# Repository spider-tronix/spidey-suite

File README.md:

# spidey-suite

spidey suite is the smart choice for Over The Air(OTA) Programming solution for your AVR microcontrollers. It has products ranging from bootloader to code uploader/downloader for your device, all in the same module.

## Products 

spidey suite has 3 products to offer and they are- 
- ```spideyboot``` - A small light weight bootloader with just the OTA Programmming functionality. More info [here](https://github.com/spider-tronix/spidey-suite/tree/master/spideyboot)
- ```spideydude``` - Code uploader for spideyboot. More info [here](https://github.com/spider-tronix/spidey-suite/tree/master/spideydude)
- ```spideyAVRdude``` - OTA code uploader for the boards having Arduino's Optiboot bootloader. More info [here](https://github.com/spider-tronix/spidey-suite/tree/master/spideyAVRdude)

## Contents of this repository

> To be updated

## Bug Reports and Improvements

-  To report a ***bug*** in the software or to request *an enhancement*, create an [*issue*](https://github.com/spider-tronix/spidey-suite/issues) clearly stating the problem. Our team will look into the problem and will fix it as soon as possible.

- To suggest *changes/improvements*, create a [*pull-request*](https://github.com/spider-tronix/spidey-suite/pulls) with the modified files. Upon successfully validating the changes by us, the suggested changes will be added to the repository.

## Website

Click [**here**](https://spider-tronix.github.io/spidey-suite/) to navigate to the website. 

The website is developed and maintained by our team only. It uses a number of web development tech and those are:

* [ReactJS](https://reactjs.org/) - React is an open-source, front end, JavaScript library for building user interfaces or UI components.
* [Bootstrap](https://getbootstrap.com/) - Bootstrap is a free and open-source CSS framework directed at responsive, mobile-first front-end web development.
* [jQuery](https://jquery.com/) - jQuery is an open-source, free JavaScript library designed to simplify HTML DOM tree traversal and manipulation, as well as event handling, CSS animation, and Ajax

For more info on the website, click [here](https://github.com/spider-tronix/spidey-suite/tree/master/Build/Code/Web/spidey-suite).

## Credits

spidey suite is an open source project started by [**Spider Tronix**](https://spider-tronix.github.io/) profile under [**Spider R&D Club**](https://spider.nitt.edu/) of **NIT Trichy**.

The spidey suite team is composed of [Aditya Kumar Singh](https://github.com/adityasingh3007), [Miriam](https://github.com/Githubmsk), [Arunesh Saddish](https://github.com/arunesh006), [N Srikrishna](https://github.com/2001srikrishna)

# PROJECT UNDER DEVELOPMENT PHASE

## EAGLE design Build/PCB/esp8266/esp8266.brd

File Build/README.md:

# Build
This folder contains the build(source) files for the various products under spidey suite.  

# spidey suite
A module to add OTA Programming functionality to AVR Microcontrollers

## Abstract
OTA (Over the Air) Programming is a process which allows devices to upgrade their firmware or software wirelessly without any physical access. It uses wireless technology like Wi-Fi, Bluetooth, GPRS or 4G/3G rather than wired serial communication. OTA is used to reprogram the devices like microcontrollers, cell phones, computers, set-top box etc in order to add some feature, resolve some bugs, etc. The project aims to make a module which can be attached to any AVR microcontroller in order to add OTA Programming feature to it. The module will be just like any other peripheral sensor modules with few pins left open for the user to connect it to their circuit. The module will be cost effective and as minimum space consuming as possible. Also, a web portal will be developed where in the corresponding codes for the target μC for example – Arduino UNO/Mega/Nano can be downloaded and configured as per the user’s requirement. And a dedicated HTTP interface wherein the codes can be sent over the air.

# Status
#### Phase 1:
- Understanding complete memory architecture of a μC
- Understanding bootloader, how OTA works.
- How a program is transferred in the μC. 
- How to write a light weight custom bootloader which can be added on top of an existing bootloader so that the μC can still be programmed from Arduino IDE (if using Arduino boards). 
- If that’s not feasible (considering memory consumption by two bootloaders), how to write a standalone bootloader. 

#### Phase 2:
- Implementing the understanding done in the previous phase in the UNO and Mega boards. 
- Developing the portal
- Generalising the code in order to target more than 1 μC with the same code if possible (due to same architecture) 

# Team:
  - Aditya Kumar Singh [https://github.com/adityasingh3007] 
  - Miriam [https://github.com/Githubmsk]
  - Arunesh Saddish [https://github.com/arunesh006]
  - N Srikrishna [https://github.com/2001srikrishna]

## NOTE: Project under development phase.

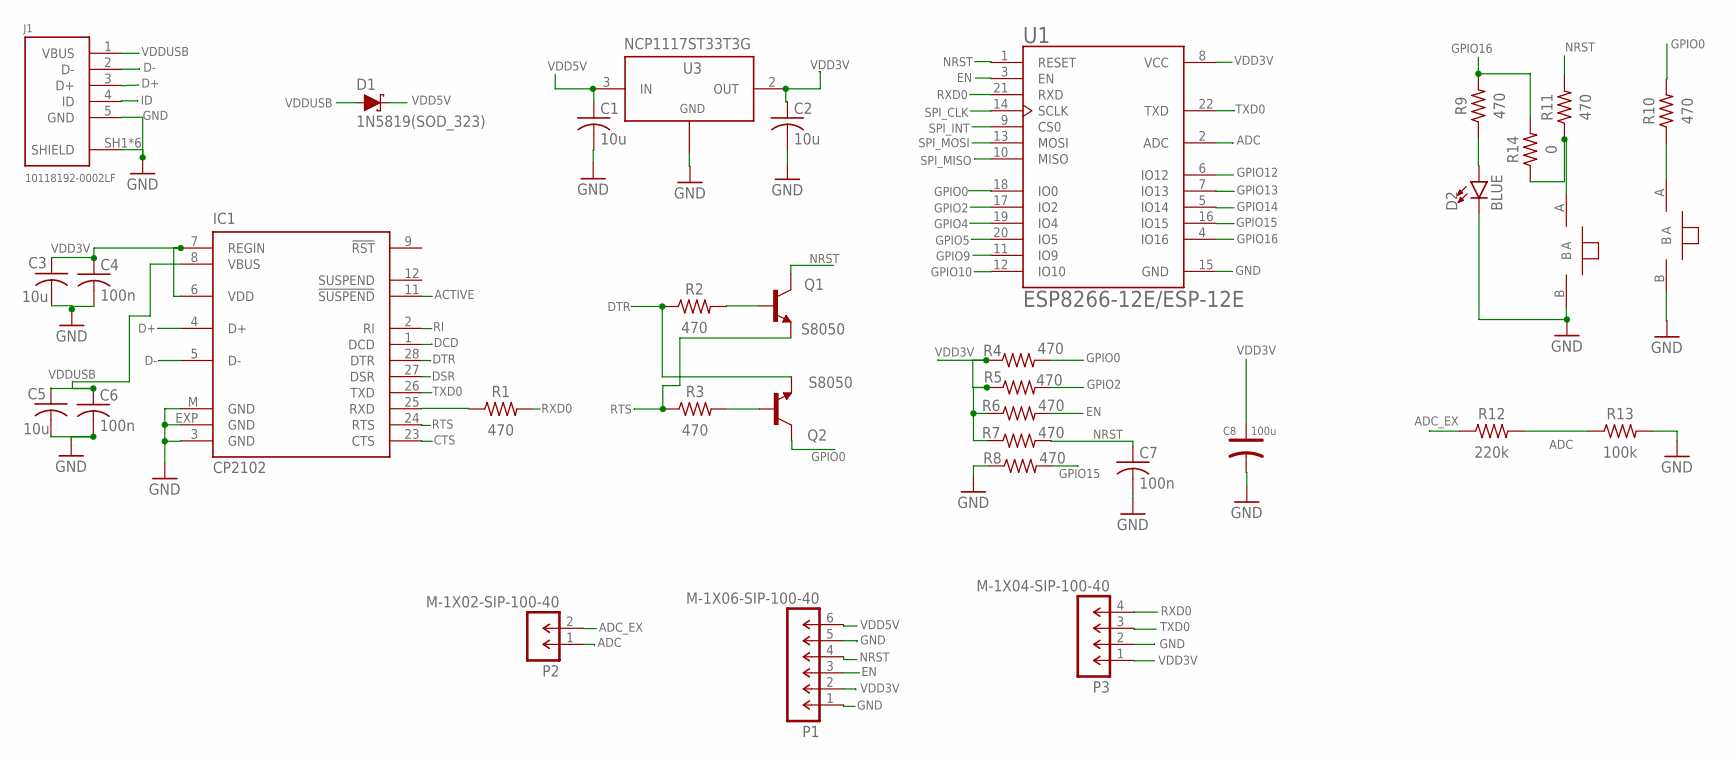
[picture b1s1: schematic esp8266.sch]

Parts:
C1: 10u; CAPC2012X110
C2, C3, C5: 10u; CAPC1005X60
C4, C6, C7: 100n; CAPC1005X60
C8: 100u; AVX-B
D1: 1N5819(SOD_323); SOD-323
D2: BLUE; LED-0603
IC1: CP2102; MLP28
J1: 10118192-0002LF
P1: M-1X06-SIP-100-40; SIP-100-06-40
P2: M-1X02-SIP-100-40; SIP-100-02-40
P3: M-1X04-SIP-100-40; SIP-100-04-40
Q1, Q2: S8050; SOT23
R1, R2, R3, R4, R5, R6, R7, R8, R9, R10, R11: 470; RESC1005X40
R12: 220k; RESC1005X40
R13: 100k; RESC1005X40
R14: 0; RESC1005X40
U1: ESP8266-12E/ESP-12E; XCVR_ESP8266-12E/ESP-12E
U3: NCP1117ST33T3G; SOT-223
U$2, U$3: PT_820

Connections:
ACTIVE: IC1.11 (!SUSPEND)
ADC: P2.1, R12.2, R13.1, U1.2 (ADC)
ADC_EX: P2.2, R12.1
CTS: IC1.23 (CTS)
D+: IC1.4 (D+), J1.3 (D+)
D-: IC1.5 (D-), J1.2 (D-)
DCD: IC1.1 (DCD)
DSR: IC1.27 (DSR)
DTR: IC1.28 (DTR), Q2.2 (E), R2.1
EN: P1.3, R6.2, U1.3 (EN)
GND: C1.2, C2.2, C3.2, C4.2, C5.2, C6.2, C7.2, C8.-, D2.C, IC1.3 (GND), IC1.EXP (GND), IC1.M (GND), J1.5 (GND), J1.SH1 (SHIELD), J1.SH2 (SHIELD), J1.SH3 (SHIELD), J1.SH4 (SHIELD), J1.SH5 (SHIELD), J1.SH6 (SHIELD), P1.1, P1.5, P3.2, R8.1, R13.2, U1.15 (GND), U3.1 (ADJ/GND), U$2.B, U$3.B
GPIO0: Q2.3 (C), R4.2, R10.2, U1.18 (IO0)
GPIO2: R5.2, U1.17 (IO2)
GPIO4: U1.19 (IO4)
GPIO5: U1.20 (IO5)
GPIO9: U1.11 (IO9)
GPIO10: U1.12 (IO10)
GPIO12: U1.6 (IO12)
GPIO13: U1.7 (IO13)
GPIO14: U1.5 (IO14)
GPIO15: R8.2, U1.16 (IO15)
GPIO16: R9.2, R14.2, U1.4 (IO16)
ID: J1.4 (ID)
unnamed: D2.A, R9.1
unnamed: Q1.1 (B), R2.2
unnamed: R11.1, R14.1, U$2.A
unnamed: Q2.1 (B), R3.2
unnamed: R10.1, U$3.A
NRST: C7.1, P1.4, Q1.3 (C), R7.2, R11.2, U1.1 (RESET)
RI: IC1.2 (RI)
RTS: IC1.24 (RTS), Q1.2 (E), R3.1
RX: IC1.25 (RXD), R1.1
RXD0: P3.4, R1.2, U1.21 (RXD)
SPI_CLK: U1.14 (SCLK)
SPI_INT: U1.9 (CS0)
SPI_MISO: U1.10 (MISO)
SPI_MOSI: U1.13 (MOSI)
TXD0: IC1.26 (TXD), P3.3, U1.22 (TXD)
VDD3V: C2.1, C3.1, C4.1, C8.+, IC1.6 (VDD), IC1.7 (REGIN), P1.2, P3.1, R4.1, R5.1, R6.1, R7.1, U1.8 (VCC), U3.2 (OUT), U3.4
VDD5V: C1.1, D1.C, P1.6, U3.3 (IN)
VDDUSB: C5.1, C6.1, D1.A, IC1.8 (VBUS), J1.1 (VBUS)

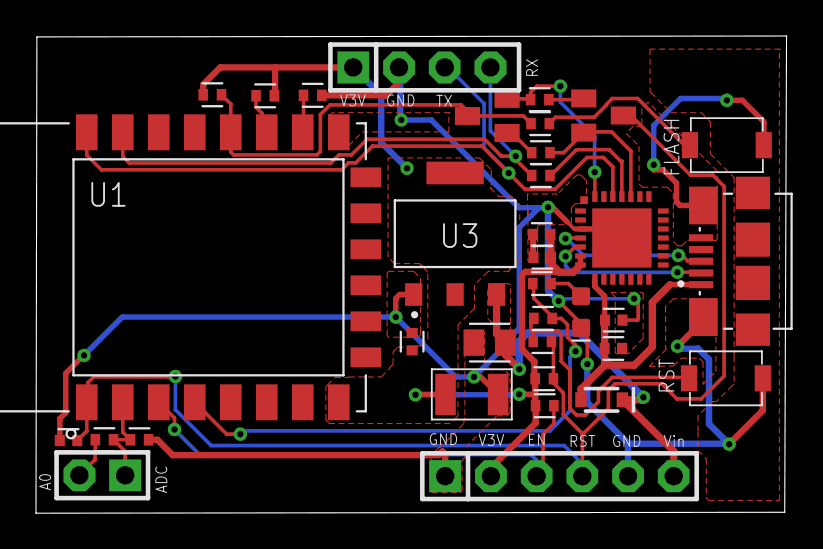
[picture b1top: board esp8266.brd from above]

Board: 2 copper layers, 41.7 x 26.5 mm, 35 parts (0 on the bottom side), 24 nets.

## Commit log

2020-09-22 Resources, gitignore added. Readme updated
2020-09-22 Github profile link added
2020-09-25 Code to read signature and fuse bytes added
2020-09-27 Few other resources added
2020-09-27 Basic fixed prog. bootloader code added
2020-09-29 AVRDUDE executable added
2020-09-29 BLDR base testing code added
2020-09-29 Cheatsheet for avrdude added
2020-09-29 avrdude cheatsheet errro fixed. Basic_BLDR code logic modified:
2020-10-02 Checking MCUSR reg logic added
2020-10-04 Server files for transferring HEX file added
2020-10-05 EXTRF logic rectified
2020-10-08 usart func added
2020-10-08 Optiboot logic txt file, esp32 softAP mode code added
2020-10-09 ESP32 server client code for uploading hex file added
2020-10-09 UART Reciever Code Rectified
2020-10-10 UART and Watchdog utility codes added
2020-10-11 ESP32 SPIFFS file uploading via station mode code added
2020-10-12 Code having AP+STA feature added. STA standalone code credentials fixed.
2020-10-16 Routing corner cases logic added
2020-10-16 avrdude replica for esp32 base code added
2020-10-18 avrdude client code converted to lib files. Snip of output added
2020-10-19 SpideyBoot code for ESP32 added
2020-10-19 SpideyBoot for esp32 renamed to Spideydude
2020-10-19 Spideydude HTTP Server added
2020-10-19 Spideyboot bootloader code added
2020-10-19 SpideyBoot Code Added
2020-10-20 Spideyserver lib file for Spideydude added. Helper .py and .htm files added
2020-10-20 spideydude verbose sent as reponse to server part added
2020-10-21 Optiboot logic updated
2020-10-22 response sending data back to server part added
2020-10-24 Code to get Signature Bytes and Read a page from flash added in SpideyBoot
2020-10-25 Phase 2 initiated. Readme updated
2020-10-25 gitignore added
2020-10-25 Spideyboot program to read flash updated
2020-10-25 Web portal base added
2020-10-26 spideydude protocol lib changes added
2020-10-26 Contribute and Footer section added
2020-10-26 spideydude read signature bytes logic added
2020-10-27 Read Flash Error and Spidey Protocol Updated
2020-10-27 SpideyProtocol Updated
2020-10-27 WATCHDOG timer code documented.
2020-10-27 Product section added. Footer bug fixed. Minor UI change
2020-10-29 Hex parser v.0
2020-10-29 maximum bootsize and optiboot usage data added to signature .ino
2020-10-29 minor changes
2020-10-31 Organizing directories
2020-10-31 Readmes updated
2020-10-31 Typo fixed
2020-10-31 WDG and UART Lib Merged
2020-10-31 Code to Check Flash Corrected
2020-11-01 Web portal Feature and Product section added. Name changing done
2020-11-01 LICENSE added
2020-11-02 HexParser testing code
2020-11-04 Protocol.md and Code documentation added
2020-11-05 Documentation enhanced. Minor bug fixed
2020-11-05 Updated HexParser
2020-11-05 Spideyboot production code added. Protocol.md modified
2020-11-07 HEX Parser data handling bug fixed. Hex parser added to spideydude. Addressing bug fix in spideydude.
2020-11-13 the helper library with the signchk and bytetohex func
2020-12-10 Signature verification added in Spideydude
2020-12-10 Spideydude v0.9.2 production code added
2020-12-10 hexParser and Signature module added to esp32_avrdude
2020-12-11 Updated PROTOCOL.md
    Fixed typos and confusing statements.
2020-12-11 Updated main README and Build/Readme
2020-12-11 Dupicates removed. SpideyAVRdude production coded added
2020-12-12 Spideyboot: Optimized the pagelength data storing -v0.7.0 update
2020-12-13 Flash Size check, auto pageSize detection added
2020-12-17 Prod. dropped. PCB for the mdoule added
2020-12-23 Images added. Readme updated
2020-12-23 Update readme with images link
2020-12-29 Readmes updated. Images and sample hex codes added
2020-12-29 spideybootd readme updated. Sample hex file added
2021-01-19 Minor broken links fixed
2021-01-19 Minor broken links fixed.
2021-01-21 Webpage header added. Other minor improvements

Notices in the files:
parts and their libraries:
SparkFun-DiscreteSemi: Licensing: Creative Commons ShareAlike 4.0 International - https://creativecommons.org/licenses/by-sa/4.0
con-headers-jp: Copyright (C) 2008, Bob Starr
